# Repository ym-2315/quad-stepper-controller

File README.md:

# Quad Stepper Controller (THT only)
This is my **first PCB design attempt** using KiCad.  
It’s a **quad stepper motor controller** built with only **through-hole components (THT)** that I had available.  

##  Features
- Controls up to 4 stepper motors
- Built using common THT components
- Simple design, good for learning PCB layout and stepper interfacing

##  Repository
- `kicad/` → KiCad source files (`.kicad_sch`, `.kicad_pcb`, etc.)
- `outputs/` → Generated files (Gerbers, BOM, PDFs)
- `images/` → Screenshots and 3D renders

##  Notes
- This is my first attempt at PCB design.
- Not tested or manufactured yet.
- Feedback and suggestions are welcome!

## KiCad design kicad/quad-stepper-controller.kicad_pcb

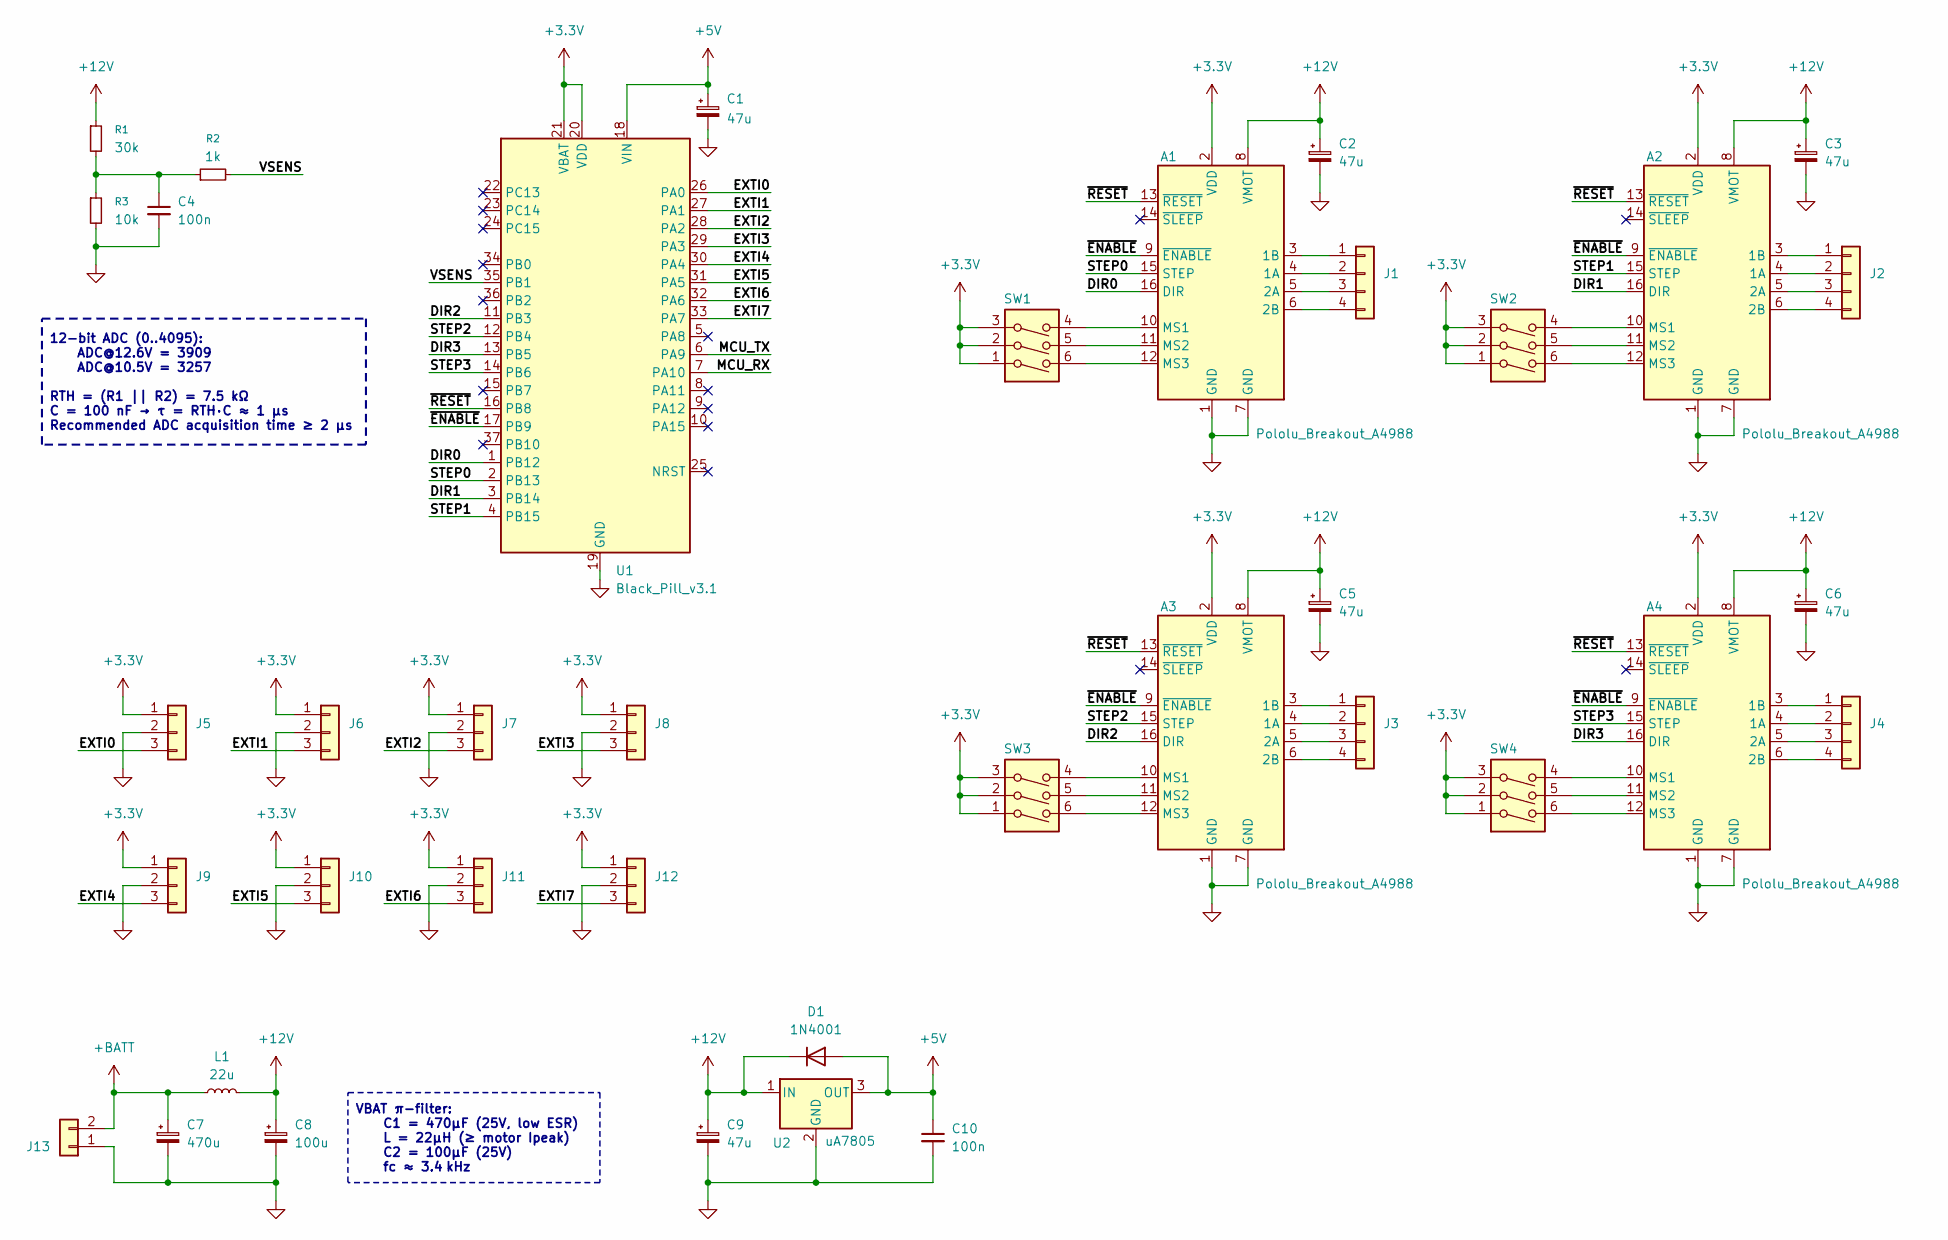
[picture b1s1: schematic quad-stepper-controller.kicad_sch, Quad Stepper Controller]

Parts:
A1, A2, A3, A4: Pololu_Breakout_A4988; Pololu_Breakout-16_15.2x20.3mm
C1, C2, C3, C5, C6, C9: 47u; CP_Radial_D5.0mm_P2.50mm
C4: 100n; C_Disc_D5.0mm_W2.5mm_P2.50mm
C7: 470u; CP_Radial_D10.0mm_P5.00mm
C8: 100u; CP_Radial_D10.0mm_P5.00mm
C10: 100n; CP_Radial_D5.0mm_P2.50mm
D1: 1N4001; D_DO-41_SOD81_P10.16mm_Horizontal
J1, J2, J3, J4: Conn_01x04; JST_XH_B4B-XH-AM_1x04_P2.50mm_Vertical
J5, J6, J7, J8, J9, J10, J11, J12: Conn_01x03; PinHeader_1x03_P2.54mm_Vertical
J13: Conn_01x02; AMASS_XT60-M_1x02_P7.20mm_Vertical
L1: 22u; L_Radial_D12.0mm_P10.00mm_Neosid_SD12_style1
R1: 30k; R_Axial_DIN0204_L3.6mm_D1.6mm_P7.62mm_Horizontal
R2: 1k; R_Axial_DIN0204_L3.6mm_D1.6mm_P7.62mm_Horizontal
R3: 10k; R_Axial_DIN0204_L3.6mm_D1.6mm_P7.62mm_Horizontal
SW1, SW2, SW3, SW4: SW_DIP_x03; SW_DIP_SPSTx03_Slide_9.78x9.8mm_W7.62mm_P2.54mm
U1: Black_Pill_v3.1
U2: uA7805; TO-220-3_Vertical

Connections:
+3.3V: A1.2 (VDD), A2.2 (VDD), A3.2 (VDD), A4.2 (VDD), J5.1, J6.1, J7.1, J8.1, J9.1, J10.1, J11.1, J12.1, SW1.1, SW1.2, SW1.3, SW2.1, SW2.2, SW2.3, SW3.1, SW3.2, SW3.3, SW4.1, SW4.2, SW4.3, U1.20 (VDD), U1.21 (VBAT), U1.38 (VDD)
+5V: C1.1, C10.1, D1.2 (A), U1.18 (VIN), U1.40 (VIN), U2.3 (OUT)
+12V: A1.8 (VMOT), A2.8 (VMOT), A3.8 (VMOT), A4.8 (VMOT), C2.1, C3.1, C5.1, C6.1, C8.1, C9.1, D1.1 (K), L1.2, R1.1, U2.1 (IN)
+BATT: C7.1, J13.2, L1.1
/DIR0: A1.16 (DIR), U1.1 (PB12)
/DIR1: A2.16 (DIR), U1.3 (PB14)
/DIR2: A3.16 (DIR), U1.11 (PB3)
/DIR3: A4.16 (DIR), U1.13 (PB5)
/EXTI0: J5.3, U1.26 (PA0)
/EXTI1: J6.3, U1.27 (PA1)
/EXTI2: J7.3, U1.28 (PA2)
/EXTI3: J8.3, U1.29 (PA3)
/EXTI4: J9.3, U1.30 (PA4)
/EXTI5: J10.3, U1.31 (PA5)
/EXTI6: J11.3, U1.32 (PA6)
/EXTI7: J12.3, U1.33 (PA7)
/MCU_RX: U1.7 (PA10)
/MCU_TX: U1.6 (PA9)
/STEP0: A1.15 (STEP), U1.2 (PB13)
/STEP1: A2.15 (STEP), U1.4 (PB15)
/STEP2: A3.15 (STEP), U1.12 (PB4)
/STEP3: A4.15 (STEP), U1.14 (PB6)
/VSENS: R2.2, U1.35 (PB1)
/~ENABLE: A1.9 (~ENABLE), A2.9 (~ENABLE), A3.9 (~ENABLE), A4.9 (~ENABLE), U1.17 (PB9)
/~RESET: A1.13 (~RESET), A2.13 (~RESET), A3.13 (~RESET), A4.13 (~RESET), U1.16 (PB8)
GND: A1.1 (GND), A1.7 (GND), A2.1 (GND), A2.7 (GND), A3.1 (GND), A3.7 (GND), A4.1 (GND), A4.7 (GND), C1.2, C2.2, C3.2, C4.2, C5.2, C6.2, C7.2, C8.2, C9.2, C10.2, J5.2, J6.2, J7.2, J8.2, J9.2, J10.2, J11.2, J12.2, J13.1, R3.2, U1.19 (GND), U1.39 (GND), U2.2 (GND)
unnamed: A1.4 (1A), J1.2
unnamed: A1.3 (1B), J1.1
unnamed: A1.5 (2A), J1.3
unnamed: A1.6 (2B), J1.4
unnamed: A1.10 (MS1), SW1.4
unnamed: A1.11 (MS2), SW1.5
unnamed: A1.12 (MS3), SW1.6
unnamed: A2.4 (1A), J2.2
unnamed: A2.3 (1B), J2.1
unnamed: A2.5 (2A), J2.3
unnamed: A2.6 (2B), J2.4
unnamed: A2.10 (MS1), SW2.4
unnamed: A2.11 (MS2), SW2.5
unnamed: A2.12 (MS3), SW2.6
unnamed: A3.4 (1A), J3.2
unnamed: A3.3 (1B), J3.1
unnamed: A3.5 (2A), J3.3
unnamed: A3.6 (2B), J3.4
unnamed: A3.10 (MS1), SW3.4
unnamed: A3.11 (MS2), SW3.5
unnamed: A3.12 (MS3), SW3.6
unnamed: A4.4 (1A), J4.2
unnamed: A4.3 (1B), J4.1
unnamed: A4.5 (2A), J4.3
unnamed: A4.6 (2B), J4.4
unnamed: A4.10 (MS1), SW4.4
unnamed: A4.11 (MS2), SW4.5
unnamed: A4.12 (MS3), SW4.6
unnamed: C4.1, R1.2, R2.1, R3.1

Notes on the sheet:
12-bit ADC (0..4095): ADC@12.6V = 3909 ADC@10.5V = 3257 RTH = (R1 || R2) = 7.5 kΩ C = 100 nF → τ = RTH·C ≈ 1 µs Recommended ADC acquisition time ≥ 2 µs
VBAT π-filter: C1 = 470µF (25V, low ESR) L = 22µH (≥ motor Ipeak) C2 = 100µF (25V) fc ≈ 3.4 kHz

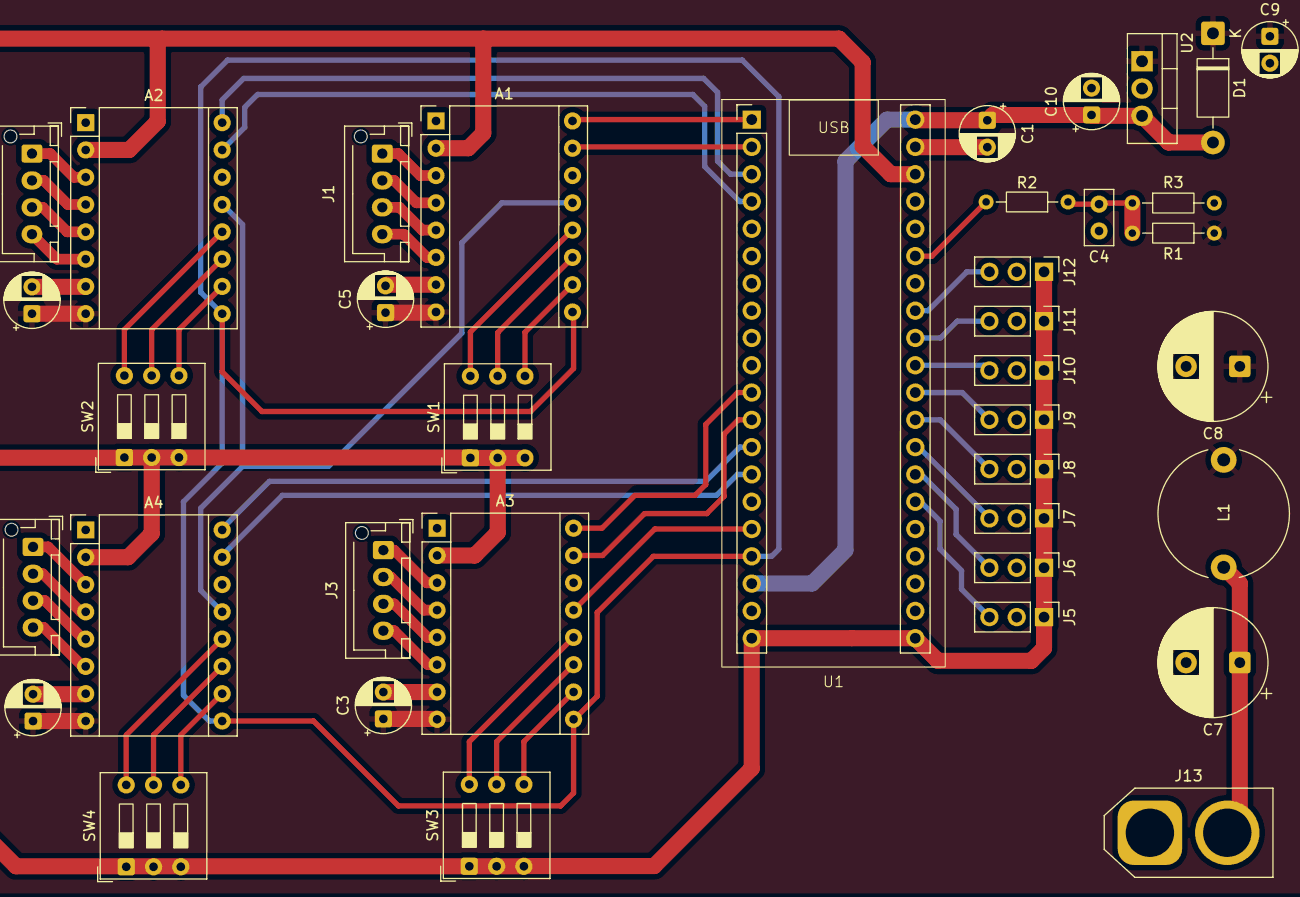
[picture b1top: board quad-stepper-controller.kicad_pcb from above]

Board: 2 copper layers, 38 parts (0 on the bottom side), 53 nets.

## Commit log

2025-09-10 Initial commit: first KiCad PCB attempt (Quad Stepper Controller)
